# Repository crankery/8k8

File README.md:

# 8k8
Intel 8008 SBC

This is just a layout of https://github.com/jim11662418/8008-SBC

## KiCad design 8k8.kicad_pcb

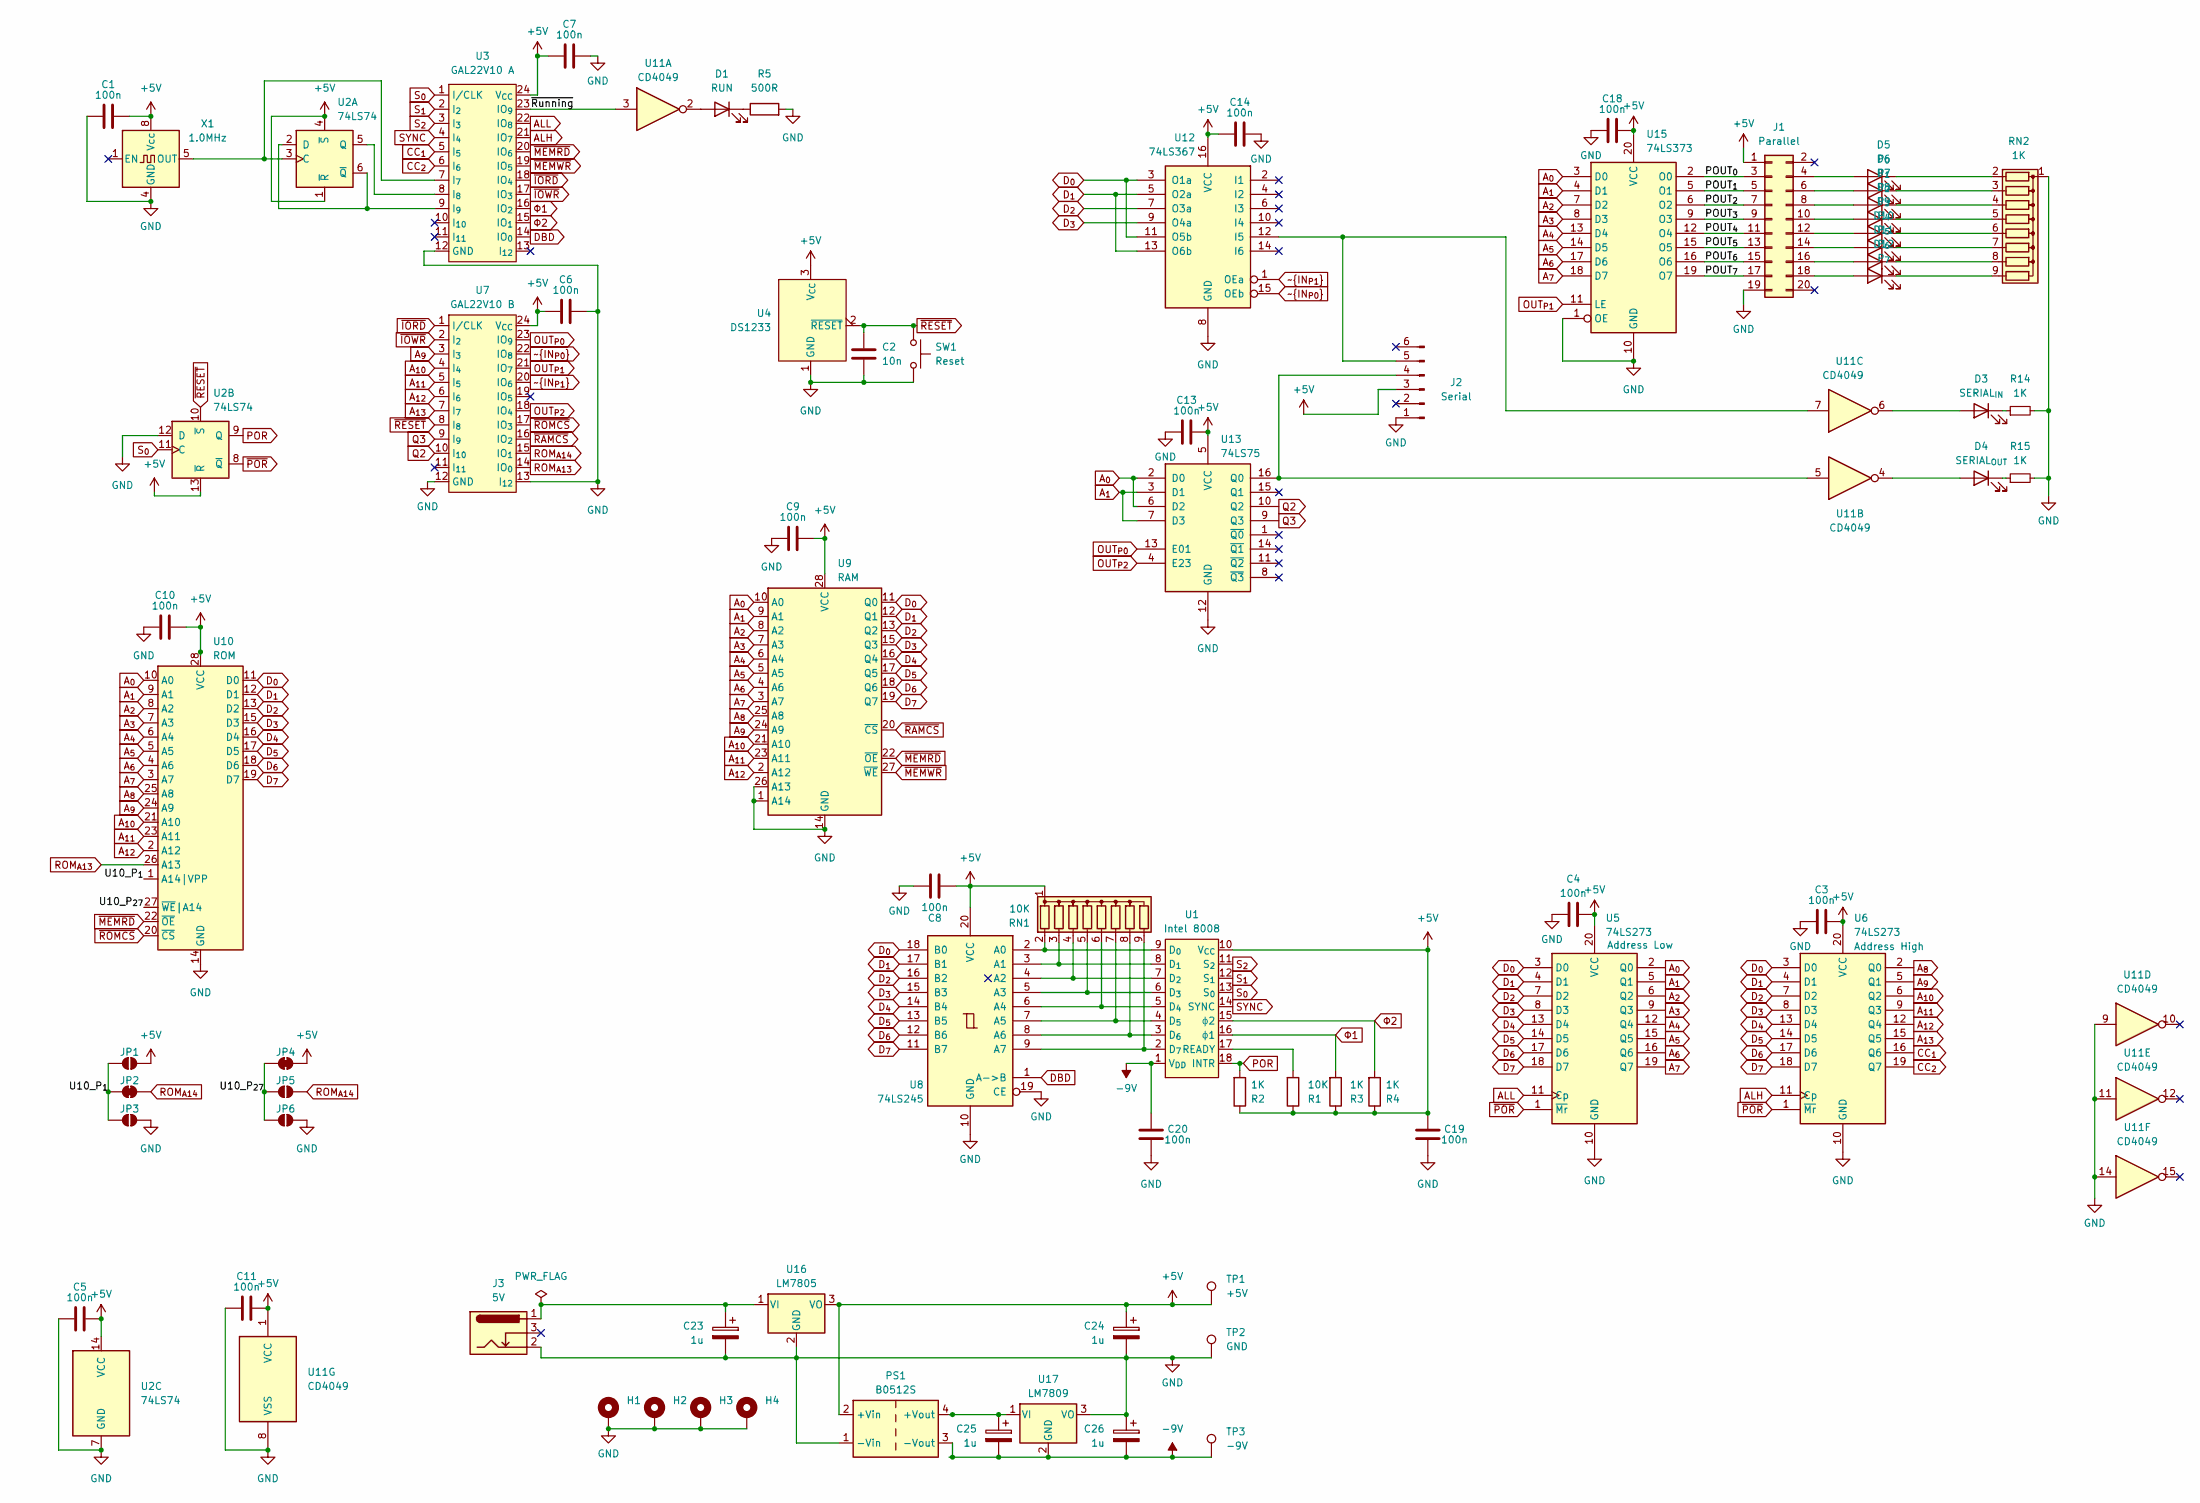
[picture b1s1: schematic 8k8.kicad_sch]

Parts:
C1, C3, C4, C5, C6, C7, C8, C9, C10, C11, C13, C14, C18, C19, C20: 100n; C_Disc_D3.0mm_W1.6mm_P2.50mm
C2: 10n; C_Disc_D3.0mm_W1.6mm_P2.50mm
C23, C24, C25, C26: 1u; CP_Radial_D5.0mm_P2.50mm
D1: RUN; LED_D3.0mm
D3: SERIAL_{IN}; LED_D3.0mm
D4: SERIAL_{OUT}; LED_D3.0mm
D5: P_{0}; LED_D3.0mm
D6: P_{1}; LED_D3.0mm
D7: P_{2}; LED_D3.0mm
D8: P_{3}; LED_D3.0mm
D9: P_{4}; LED_D3.0mm
D10: P_{5}; LED_D3.0mm
D11: P_{6}; LED_D3.0mm
D12: P_{7}; LED_D3.0mm
H1, H2, H3, H4: MountingHole_Pad; MountingHole_3.2mm_M3_DIN965_Pad
J1: Parallel; PinHeader_2x10_P2.54mm_Vertical
J2: Serial; PinHeader_1x06_P2.54mm_Vertical
J3: 5V; BarrelJack_Horizontal
JP1: 1-VCC; SolderJumper-2_P1.3mm_Open_RoundedPad1.0x1.5mm
JP2: 1-A14; SolderJumper-2_P1.3mm_Bridged_RoundedPad1.0x1.5mm
JP3: 1-GND; SolderJumper-2_P1.3mm_Open_RoundedPad1.0x1.5mm
JP4: 27-VCC; SolderJumper-2_P1.3mm_Bridged_RoundedPad1.0x1.5mm
JP5: 27-A14; SolderJumper-2_P1.3mm_Open_RoundedPad1.0x1.5mm
JP6: 27-GND; SolderJumper-2_P1.3mm_Open_RoundedPad1.0x1.5mm
PS1: B0512S; Converter_DCDC_Murata_MEE1SxxxxSC_THT
R1: 10K; R_Axial_DIN0204_L3.6mm_D1.6mm_P7.62mm_Horizontal
R2, R3, R4, R14, R15: 1K; R_Axial_DIN0204_L3.6mm_D1.6mm_P7.62mm_Horizontal
R5: 500R; R_Axial_DIN0204_L3.6mm_D1.6mm_P7.62mm_Horizontal
RN1: 10K; R_Array_SIP9
RN2: 1K; R_Array_SIP9
SW1: Reset; SW_Tactile_SPST_Angled_PTS645Vx58-2LFS
TP1: +5V; TestPoint_THTPad_1.0x1.0mm_Drill0.5mm
TP2: GND; TestPoint_THTPad_1.0x1.0mm_Drill0.5mm
TP3: -9V; TestPoint_THTPad_1.0x1.0mm_Drill0.5mm
U1: Intel 8008; DIP-18_W7.62mm
U2: 74LS74; DIP-14_W7.62mm
U3: GAL22V10 A; DIP-24_W7.62mm
U4: DS1233; TO-92_HandSolder
U5, U6: 74LS273; DIP-20_W7.62mm
U7: GAL22V10 B; DIP-24_W7.62mm
U8: 74LS245; DIP-20_W7.62mm
U9: RAM; DIP-28_W15.24mm
U10: ROM; DIP-28_W15.24mm
U11: CD4049; DIP-16_W7.62mm
U12: 74LS367; DIP-16_W7.62mm
U13: 74LS75; DIP-16_W7.62mm
U15: 74LS373; DIP-20_W7.62mm
U16: LM7805; TO-220-3_Vertical
U17: LM7809; TO-220-3_Vertical
X1: 1.0MHz; Oscillator_DIP-8

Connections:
+5V: C1.1, C3.2, C4.2, C5.2, C6.2, C7.2, C8.2, C9.2, C10.2, C11.2, C13.2, C14.2, C18.2, C19.2, C24.1, J1.1, J2.3, JP1.2 (B), JP4.2 (B), PS1.2 (+Vin), R1.1, R2.1, R3.1, R4.1, RN1.1 (common), TP1.1, U1.10 (V_{CC}), U2.1 (~R), U2.4 (~S), U2.13 (~R), U2.14 (VCC), U3.24 (V_{CC}), U4.3 (V_{CC}), U5.20 (VCC), U6.20 (VCC), U7.24 (V_{CC}), U8.20 (VCC), U9.28 (VCC), U10.28 (VCC), U11.1 (VCC), U12.16 (VCC), U13.5 (VCC), U15.20 (VCC), U16.3 (VO), X1.8 (Vcc)
-9V: C20.2, C25.2, C26.2, PS1.3 (-Vout), TP3.1, U1.1 (V_{DD}), U17.2 (GND)
/POUT_{0}: J1.3, U15.2 (O0)
/POUT_{1}: J1.5, U15.5 (O1)
/POUT_{2}: J1.7, U15.6 (O2)
/POUT_{3}: J1.9, U15.9 (O3)
/POUT_{4}: J1.11, U15.12 (O4)
/POUT_{5}: J1.13, U15.15 (O5)
/POUT_{6}: J1.15, U15.16 (O6)
/POUT_{7}: J1.17, U15.19 (O7)
/U10_P_{1}: JP1.1 (A), JP2.1 (A), JP3.1 (A), U10.1 (A14|VPP)
/U10_P_{27}: JP4.1 (A), JP5.1 (A), JP6.1 (A), U10.27 (~WE|A14)
/~Running: U3.23 (IO_{9}), U11.3
ALH: U3.21 (IO_{7}), U6.11 (Cp)
ALL: U3.22 (IO_{8}), U5.11 (Cp)
A_{0}: U5.2 (Q0), U9.10 (A0), U10.10 (A0), U13.2 (D0), U13.6 (D2), U15.3 (D0)
A_{1}: U5.5 (Q1), U9.9 (A1), U10.9 (A1), U13.3 (D1), U13.7 (D3), U15.4 (D1)
A_{2}: U5.6 (Q2), U9.8 (A2), U10.8 (A2), U15.7 (D2)
A_{3}: U5.9 (Q3), U9.7 (A3), U10.7 (A3), U15.8 (D3)
A_{4}: U5.12 (Q4), U9.6 (A4), U10.6 (A4), U15.13 (D4)
A_{5}: U5.15 (Q5), U9.5 (A5), U10.5 (A5), U15.14 (D5)
A_{6}: U5.16 (Q6), U9.4 (A6), U10.4 (A6), U15.17 (D6)
A_{7}: U5.19 (Q7), U9.3 (A7), U10.3 (A7), U15.18 (D7)
A_{8}: U6.2 (Q0), U9.25 (A8), U10.25 (A8)
A_{9}: U6.5 (Q1), U7.3 (I_{3}), U9.24 (A9), U10.24 (A9)
A_{10}: U6.6 (Q2), U7.4 (I_{4}), U9.21 (A10), U10.21 (A10)
A_{11}: U6.9 (Q3), U7.5 (I_{5}), U9.23 (A11), U10.23 (A11)
A_{12}: U6.12 (Q4), U7.6 (I_{6}), U9.2 (A12), U10.2 (A12)
A_{13}: U6.15 (Q5), U7.7 (I_{7})
CC_{1}: U3.5 (I_{5}), U6.16 (Q6)
CC_{2}: U3.6 (I_{6}), U6.19 (Q7)
DBD: U3.14 (IO_{0}), U8.1 (A->B)
D_{0}: U5.3 (D0), U6.3 (D0), U8.18 (B0), U9.11 (Q0), U10.11 (D0), U12.3 (O1a), U12.11 (O5b)
D_{1}: U5.4 (D1), U6.4 (D1), U8.17 (B1), U9.12 (Q1), U10.12 (D1), U12.5 (O2a), U12.13 (O6b)
D_{2}: U5.7 (D2), U6.7 (D2), U8.16 (B2), U9.13 (Q2), U10.13 (D2), U12.7 (O3a)
D_{3}: U5.8 (D3), U6.8 (D3), U8.15 (B3), U9.15 (Q3), U10.15 (D3), U12.9 (O4a)
D_{4}: U5.13 (D4), U6.13 (D4), U8.14 (B4), U9.16 (Q4), U10.16 (D4)
D_{5}: U5.14 (D5), U6.14 (D5), U8.13 (B5), U9.17 (Q5), U10.17 (D5)
D_{6}: U5.17 (D6), U6.17 (D6), U8.12 (B6), U9.18 (Q6), U10.18 (D6)
D_{7}: U5.18 (D7), U6.18 (D7), U8.11 (B7), U9.19 (Q7), U10.19 (D7)
GND: C1.2, C2.2, C3.1, C4.1, C5.1, C6.1, C7.1, C8.1, C9.1, C10.1, C11.1, C13.1, C14.1, C18.1, C19.1, C20.1, C23.2, C24.2, C26.1, H1.1, H2.1, H3.1, H4.1, J1.19, J2.1, J3.2, JP3.2 (B), JP6.2 (B), PS1.1 (-Vin), R5.2, R14.2, R15.2, RN2.1 (common), SW1.1, TP2.1, U2.7 (GND), U2.12 (D), U3.12 (GND), U4.1 (GND), U5.10 (GND), U6.10 (GND), U7.12 (GND), U7.13 (I_{12}), U8.10 (GND), U8.19 (CE), U9.1 (A14), U9.14 (GND), U9.26 (A13), U10.14 (GND), U11.8 (VSS), U11.9, U11.11, U11.14, U12.8 (GND), U13.12 (GND), U15.1 (OE), U15.10 (GND), U16.2 (GND), U17.3 (VO), X1.4 (GND)
unnamed: D1.2 (A), U11.2
unnamed: D1.1 (K), R5.1
unnamed: D3.2 (A), U11.6
unnamed: D3.1 (K), R14.1
unnamed: D4.2 (A), U11.4
unnamed: D4.1 (K), R15.1
unnamed: D5.2 (A), J1.4
unnamed: D5.1 (K), RN2.2 (R1)
unnamed: D6.2 (A), J1.6
unnamed: D6.1 (K), RN2.3 (R2)
unnamed: D7.2 (A), J1.8
unnamed: D7.1 (K), RN2.4 (R3)
unnamed: D8.2 (A), J1.10
unnamed: D8.1 (K), RN2.5 (R4)
unnamed: D9.2 (A), J1.12
unnamed: D9.1 (K), RN2.6 (R5)
unnamed: D10.2 (A), J1.14
unnamed: D10.1 (K), RN2.7 (R6)
unnamed: D11.2 (A), J1.16
unnamed: D11.1 (K), RN2.8 (R7)
unnamed: D12.2 (A), J1.18
unnamed: D12.1 (K), RN2.9 (R8)
unnamed: J2.4, U11.5, U13.16 (Q0)
unnamed: J2.5, U11.7, U12.12 (I5)
unnamed: C25.1, PS1.4 (+Vout), U17.1 (VI)
unnamed: RN1.2 (R1), U1.9 (D_{0}), U8.2 (A0)
unnamed: RN1.3 (R2), U1.8 (D_{1}), U8.3 (A1)
unnamed: RN1.4 (R3), U1.7 (D_{2}), U8.4 (A2)
unnamed: RN1.5 (R4), U1.6 (D_{3}), U8.5 (A3)
unnamed: RN1.6 (R5), U1.5 (D_{4}), U8.6 (A4)
unnamed: RN1.7 (R6), U1.4 (D_{5}), U8.7 (A5)
unnamed: RN1.8 (R7), U1.3 (D_{6}), U8.8 (A6)
unnamed: RN1.9 (R8), U1.2 (D_{7}), U8.9 (A7)
unnamed: R1.2, U1.17 (READY)
unnamed: U2.3 (C), U3.7 (I_{7}), X1.5 (OUT)
unnamed: U2.2 (D), U2.6 (~Q), U3.9 (I_{9})
unnamed: U2.5 (Q), U3.8 (I_{8})
unnamed: C23.1, J3.1, U16.1 (VI)
OUT_{P0}: U7.23 (IO_{9}), U13.13 (E01)
OUT_{P1}: U7.21 (IO_{7}), U15.11 (LE)
OUT_{P2}: U7.18 (IO_{4}), U13.4 (E23)
POR: R2.2, U1.18 (INTR), U2.9 (Q)
Q2: U7.10 (I_{10}), U13.10 (Q2)
Q3: U7.9 (I_{9}), U13.9 (Q3)
ROM_{A13}: U7.14 (IO_{0}), U10.26 (A13)
ROM_{A14}: JP2.2 (B), JP5.2 (B), U7.15 (IO_{1})
SYNC: U1.14 (SYNC), U3.4 (I_{4})
S_{0}: U1.13 (S_{0}), U2.11 (C), U3.1 (I/CLK)
S_{1}: U1.12 (S_{1}), U3.2 (I_{2})
S_{2}: U1.11 (S_{2}), U3.3 (I_{3})
~IN_{P0}: U7.22 (IO_{8}), U12.15 (OEb)
~IN_{P1}: U7.20 (IO_{6}), U12.1 (OEa)
~IORD: U3.18 (IO_{4}), U7.1 (I/CLK)
~IOWR: U3.17 (IO_{3}), U7.2 (I_{2})
~MEMRD: U3.20 (IO_{6}), U9.22 (~OE), U10.22 (~OE)
~MEMWR: U3.19 (IO_{5}), U9.27 (~WE)
~POR: U2.8 (~Q), U5.1 (~Mr), U6.1 (~Mr)
~RAMCS: U7.16 (IO_{2}), U9.20 (~CS)
~RESET: C2.1, SW1.2, U2.10 (~S), U4.2 (~RESET), U7.8 (I_{8})
~ROMCS: U7.17 (IO_{3}), U10.20 (~CS)
Φ1: R3.2, U1.16 (ϕ1), U3.16 (IO_{2})
Φ2: R4.2, U1.15 (ϕ2), U3.15 (IO_{1})

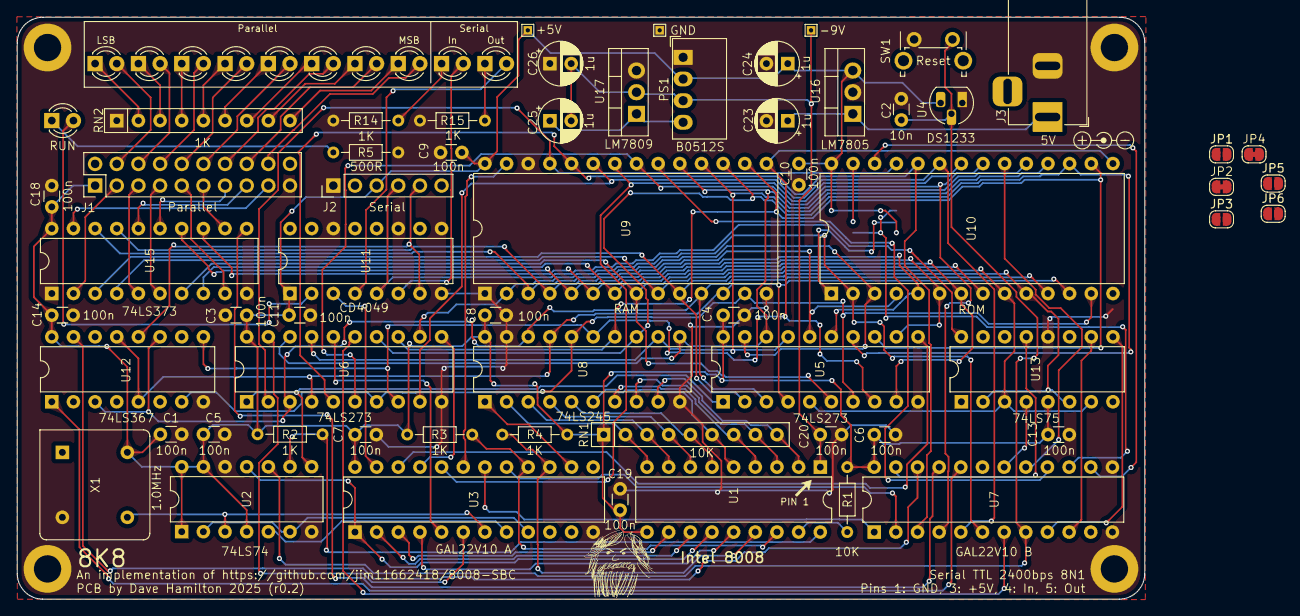
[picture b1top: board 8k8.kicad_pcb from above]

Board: 2 copper layers, 132.2 x 68.2 mm, 75 parts (0 on the bottom side), 103 nets.

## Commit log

2025-08-30 start making the rom a bit chip configurable
2025-08-30 start making the rom a bit chip configurable
    oops. i forgot to create a dev branch. yolo i guess.
